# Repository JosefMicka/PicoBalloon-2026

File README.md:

# PicoBalloon-2026
The working name of this radiosonde is PicoFalcon.

This repository contains HW design with custom antenna modelling and FW for MCU.

It is based on the popular 8-bit MCU ATmega328p. The reason of choosing this MCU was simple. It was available in my household supplies.

The air-gound communication is based on LoRaWAN. It is done by radio module RFM95 which supports LoRa CSS (Chirp Spread Spectrum) modulation.

## HW
- TBD
### PCB
- TBD
### Antennas
- TBD
#### GPS antenna
- TBD
#### ISM 868 MHz antenna
- TBD

## License

This project is distributed under several licenses depending on the component:

* **Software:** All source code is licensed under the [MIT License](LICENSE).
* **Hardware:** All hardware designs (schematics, PCB layouts, 3D models) are licensed under the [CERN-OHL-P v2](https://ohwr.org/project/cernohl/wikis/Documents/CERN-OHL-version-2) or later.
* **Documentation:** All images and documentation are licensed under [CC BY 4.0](https://creativecommons.org/licenses/by/4.0/).

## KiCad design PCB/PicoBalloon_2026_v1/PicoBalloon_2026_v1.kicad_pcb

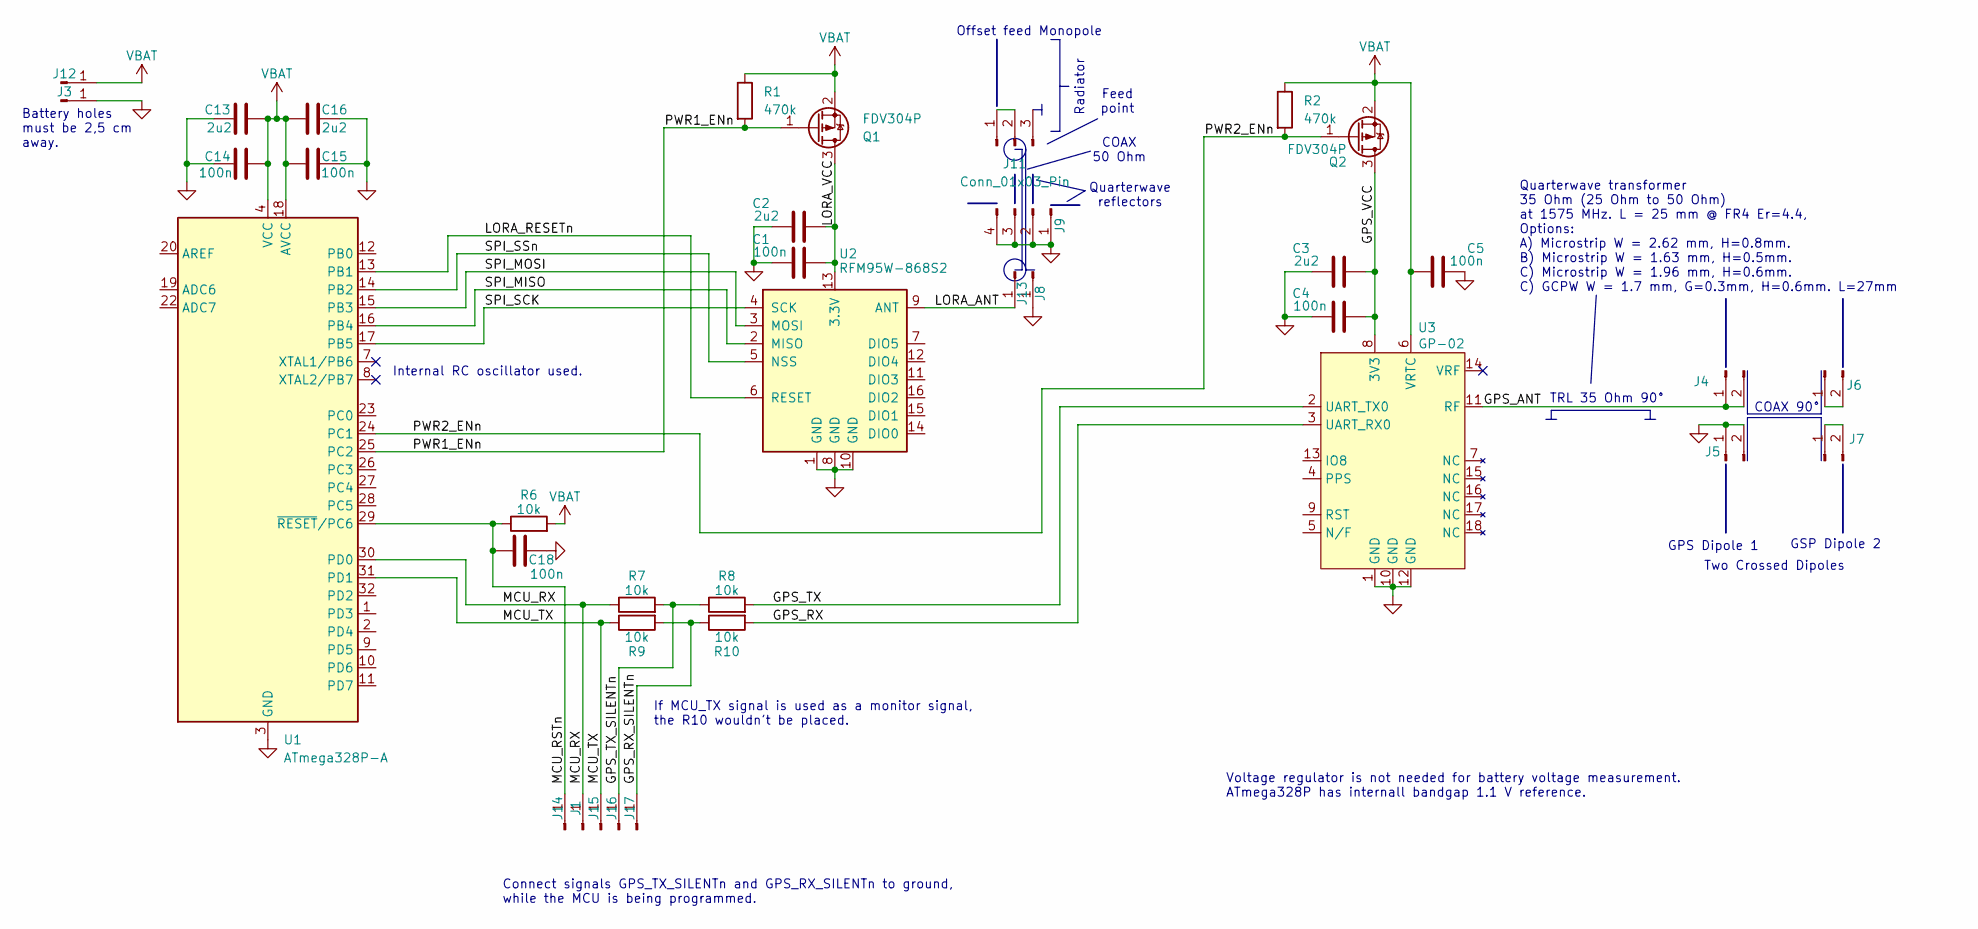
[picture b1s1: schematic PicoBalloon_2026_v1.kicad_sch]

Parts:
C1, C4, C5, C14, C15, C18: 100n; C_0805_2012Metric_Pad1.18x1.45mm_HandSolder
C2, C3, C13, C16: 2u2; C_0805_2012Metric_Pad1.18x1.45mm_HandSolder
J1, J14, J15, J16, J17: Conn_01x01_Pin; SolderWirePad_1x01_SMD_1x2mm
J3, J12: Conn_01x01_Pin; PinHeader_1x01_P2.54mm_Vertical
J4, J5, J6, J7: Conn_01x02_Pin; PinHeader_1x02_P1.27mm_Vertical
J8, J13: Conn_01x01_Pin; PinHeader_1x01_P1.27mm_Vertical
J9: Conn_01x04_Pin; PinHeader_1x04_P1.27mm_Vertical
J11: Conn_01x03_Pin; PinHeader_1x03_P1.27mm_Vertical
Q1, Q2: FDV304P; SOT-23
R1, R2: 470k; R_0805_2012Metric_Pad1.20x1.40mm_HandSolder
R6, R7, R8, R9, R10: 10k; R_0805_2012Metric_Pad1.20x1.40mm_HandSolder
U1: ATmega328P-A; TQFP-32_7x7mm_P0.8mm
U2: RFM95W-868S2; HOPERF_RFM9XW_SMD
U3: GP-02

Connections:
/GPS_ANT: J4.1, J4.2, U3.11 (RF)
/GPS_RX: R10.2, U3.3 (UART_RX0)
/GPS_RX_SILENTn: J17.1, R9.2, R10.1
/GPS_TX: R8.2, U3.2 (UART_TX0)
/GPS_TX_SILENTn: J16.1, R7.2, R8.1
/GPS_VCC: C3.2, C4.2, Q2.3 (D), U3.8 (3V3)
/LORA_ANT: J13.1, U2.9 (ANT)
/LORA_RESETn: U1.13 (PB1), U2.6 (RESET)
/LORA_VCC: C1.2, C2.2, Q1.3 (D), U2.13 (3.3V)
/MCU_RSTn: C18.2, J14.1, R6.1, U1.29 (~RESET/PC6)
/MCU_RX: J1.1, R7.1, U1.30 (PD0)
/MCU_TX: J15.1, R9.1, U1.31 (PD1)
/PWR1_ENn: Q1.1 (G), R1.2, U1.25 (PC2)
/PWR2_ENn: Q2.1 (G), R2.2, U1.24 (PC1)
/SPI_MISO: U1.16 (PB4), U2.2 (MISO)
/SPI_MOSI: U1.15 (PB3), U2.3 (MOSI)
/SPI_SCK: U1.17 (PB5), U2.4 (SCK)
/SPI_SSn: U1.14 (PB2), U2.5 (NSS)
GND: C1.1, C2.1, C3.1, C4.1, C5.1, C13.1, C14.1, C15.1, C16.1, C18.1, J3.1, J5.1, J5.2, J8.1, J9.1, J9.2, J9.3, J9.4, U1.3 (GND), U1.5 (GND), U1.21 (GND), U2.1 (GND), U2.8 (GND), U2.10 (GND), U3.1 (GND), U3.10 (GND), U3.12 (GND)
unnamed: J6.1, J6.2
unnamed: J7.1, J7.2
unnamed: J11.1, J11.2
VBAT: C5.2, C13.2, C14.2, C15.2, C16.2, J12.1, Q1.2 (S), Q2.2 (S), R1.1, R2.1, R6.2, U1.4 (VCC), U1.6 (VCC), U1.18 (AVCC), U3.6 (VRTC)

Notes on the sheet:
Connect signals GPS_TX_SILENTn and GPS_RX_SILENTn to ground, while the MCU is being programmed.
Quarterwave transformer 35 Ohm (25 Ohm to 50 Ohm) at 1575 MHz. L = 25 mm @ FR4 Er=4.4, Options: A) Microstrip W = 2.62 mm, H=0.8mm. B) Microstrip W = 1.63 mm, H=0.5mm. C) Microstrip W = 1.96 mm, H=0.6mm. C) GCPW W = 1.7 mm, G=0.3mm, H=0.6mm. L=27mm
Offset feed Monopole
COAX 50 Ohm
Quarterwave reflectors
TRL 35 Ohm 90°
Battery holes must be 2,5 cm away.
If MCU_TX signal is used as a monitor signal, the R10 wouldn't be placed.
COAX 90°
Two Crossed Dipoles
Internal RC oscillator used.
Feed point
GSP Dipole 2
Radiator
Voltage regulator is not needed for battery voltage measurement. ATmega328P has internall bandgap 1.1 V reference.
GPS Dipole 1

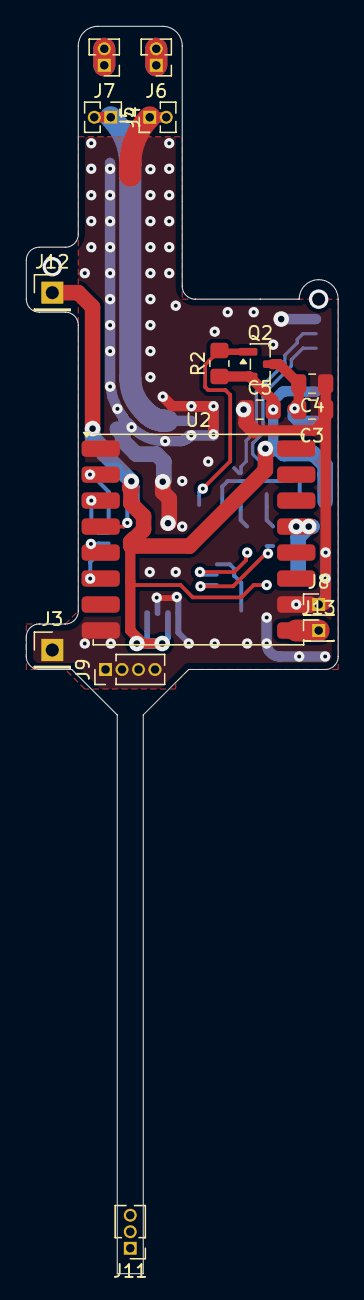
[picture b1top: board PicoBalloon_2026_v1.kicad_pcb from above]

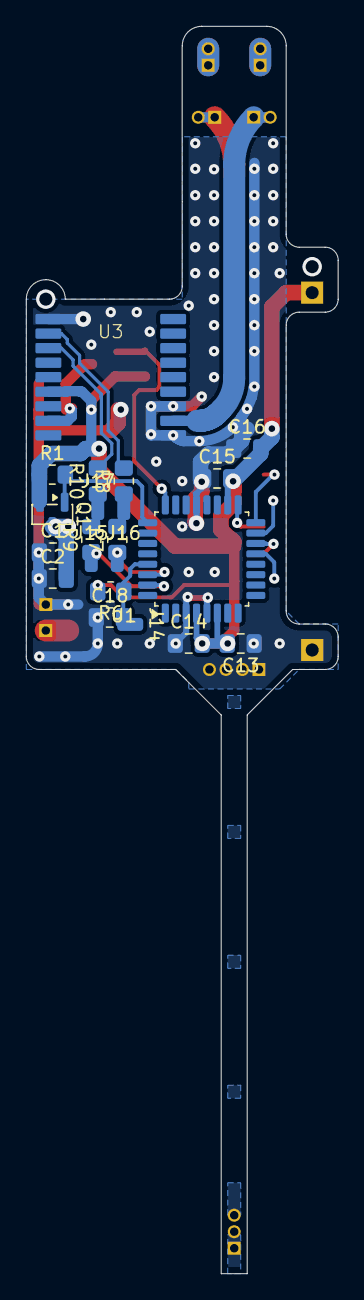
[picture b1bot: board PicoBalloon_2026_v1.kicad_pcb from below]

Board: 2 copper layers, 24.0 x 96.0 mm, 37 parts (21 on the bottom side), 23 nets.

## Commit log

2026-03-15 Update README with project details and licenses
    Expanded project description and added license information.
2026-03-16 [FW|PCB|DOCS] Initial commit.
2026-03-19 [ANT] LoRa 868 MHz optimized monopole antenna - 4NEC2 design.
2026-03-19 [ANT] GPS crossed dipoles antenna created. Slightly optimized.
2026-03-21 [ANT] Both antennas in system optimized.
2026-03-22 [ANT] Added image of the antenna system.
2026-03-23 [DOCS] TS5205 voltage regulator datasheet.
2026-03-23 [PCB] Schematic update. LoRa power on, GPS power on, VBAT meas. power on.
2026-03-25 [PCB] Schematic in progres.
2026-03-26 [PCB] Schematic drawing update.
2026-03-26 [PCB] Antennas drawings added to schematic.
2026-03-26 [PCB] PCB design begin.
2026-03-29 [PCB] PCB finished! (I hope). Not so critical signals removed. Voltage regulator removed because it is not needed.
2026-03-30 [PCB] Finished.
2026-03-31 [Sim] GPS antena impedance transformator.
2026-04-20 [ANT] 4NEC2 simulation updated according to designed antenna distance.
